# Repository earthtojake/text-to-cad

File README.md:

<div align="center">

Design physical products with AI.

[Website](https://www.texttocad.dev)

</div>

# text-to-cad

## 🚀 Quickstart

macOS and Linux:

```bash
curl -fsSL https://texttocad.dev/install.sh | sh
```

Windows, in PowerShell:

```powershell
irm https://www.texttocad.dev/install.ps1 | iex
```

It installs uv if it is missing, then sets up text-to-cad in every agent app on
your computer with each app's own commands (the plugin, which brings the skills
and CAD's MCP server, or for an agent without a plugin the skills alone; Claude
gets the skills alone and shows models in your browser),
registers the `cad` command, and moves CAD's server to the new release. Run
it again to update everything, or click CAD's update button when it shows one; it
lists the apps to restart.

Then ask your agent for a part or an assembly: it writes the model as a Python
script, runs it to build the model and shows it in the CAD viewer.

Installing by hand, app by app, and updates: [docs/install.md](docs/install.md)

## ✨ Features

The text-to-cad plugin gives your agent local workflows to generate 3D models as STEP, GLB, STL or 3MF files, check them for manufacturing, draw them, and connect to 3D printing, sheet metal and CNC services. It works with any agent that supports plugins or skills.

- [**Parts and assemblies**](skills/cad/SKILL.md): Models written as Python scripts with [build123d](https://github.com/gumyr/build123d) and [OpenCASCADE](https://github.com/Open-Cascade-SAS/OCCT), exported as STEP, STL, 3MF or GLB, and as [DXF profiles and flat patterns](skills/cad/references/2d-profiles-and-dxf.md) for laser and waterjet cutting, with joints and animations for mechanisms, and shown live in the CAD viewer.
- [**Circuit boards**](skills/pcb/SKILL.md): KiCad schematics and boards, placed and routed, checked with ERC and DRC, reviewed before you order, and exported as fabrication files.
- [**Manufacturing checks**](skills/cad/SKILL.md#can-it-be-made): Whether a part can be machined, cut and bent, molded or 3D printed, measured against the process's rules, and what to change where it cannot.
- [**Stress checks**](skills/fea/SKILL.md): Whether a part or an assembly of bonded parts holds under its loads, solved with CalculiX: each part's peak stress, safety factor and how far it moves, drawn on the model.
- [**Engineering drawings**](skills/engineering-drawing/SKILL.md): Dimensioned PDF sheets projected from the part's geometry: views, hidden lines, centre marks, hole callouts and a title block.
- [**Renders**](skills/render/SKILL.md): Photoreal stills, turntables and films of a model with Blender, lit and framed in a Python script and run on the GPU, with a quick draft before each final.
- [**Fabrication services**](skills/sendcutsend/SKILL.md): [Checks DXF and STEP files against SendCutSend's guide](skills/sendcutsend/SKILL.md) before you upload them, and [slices 3D prints](skills/print3d/SKILL.md) with OrcaSlicer and sends them to Bambu Connect or Bambu Studio.
- [**Robotics and simulation**](skills/robot-simulation/SKILL.md): Robot and world descriptions for simulation and motion planning: URDF for ROS, SRDF for MoveIt and MJCF for MuJoCo.

## 🛠️ Contributing

text-to-cad is MIT-licensed and built in the open.

- **Bugs and plugin requests**: [open an issue](https://github.com/earthtojake/text-to-cad/issues/new).
  A bug report with the model script and the output of `cad doctor --check` is the
  fastest to fix, and an agent app without a plugin gets one on request. A
  security problem is reported privately, as [SECURITY.md](SECURITY.md) says.
- **Questions, ideas and what you made**: the [Discord](https://discord.gg/5FGB9DwJYU).
  Say what the skills got wrong, too: that is what improves them.
- **Code, skills and models**: a new skill (a fabrication service, a printer, a
  CAD workflow) goes in `skills/`, an example model in `models/`, and fixes
  anywhere. [CONTRIBUTING.md](CONTRIBUTING.md) has the local setup and how to
  test in the agent apps; an agent working in the repository starts at
  [AGENTS.md](AGENTS.md).

By default, text-to-cad sends usage stats and crash reports, tagged with a random
ID and never including your files, paths or prompts. The
[privacy policy](https://www.texttocad.dev/privacy-policy) says what is sent and
how to turn it off, and the [terms of service](https://www.texttocad.dev/terms-of-service)
govern using text-to-cad.

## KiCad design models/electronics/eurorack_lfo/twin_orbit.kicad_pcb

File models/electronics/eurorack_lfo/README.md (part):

# Twin Orbit: a dual analog LFO for Eurorack, with its panel made from the board

**Build the board first.** Its KiCad files (the board, the three schematic sheets, the footprint library and the
library tables) are generated by `scripts/`, not committed: `cad run build.py`, from this folder, makes them in about
30 s. It needs the `cad` command (KiCad 10.99's kicad-cli and API come with it) and KiCad's stock libraries (macOS's
KiCad.app, or `KICAD10_SYMBOL_DIR` and `KICAD10_FOOTPRINT_DIR`). Opening the board or the schematic in the viewer
or in KiCad, the checks and the panel (`src/`) all read what it writes, so run it before any of them. The project
file, `twin_orbit.kicad_pro`, is kept: it holds the board's rules and netclasses, which no script writes.

Two voltage-controlled low-frequency oscillators in 10HP. Each has a **RATE** knob (exponential, 0.013 Hz to
80 Hz), a **CV** input that sweeps the rate, a **SHAPE** knob that crossfades triangle into square, a red/green
LED that breathes with the triangle, and **TRI**, **SQR** and **MIX** outputs. The board is a 2-layer KiCad
design; the front panel is a build123d model whose every hole is read from the board file, exported as a
laser-cut DXF and checked against SendCutSend's rules for 5052 aluminium.

**Why it is a good demo:** synth people love LFOs, and the story is the panel: *move a jack on the board and the
panel's hole moves with it*, then the panel goes straight to a fabrication service's checks.

## Where it stands

| | |
| --- | --- |
| Schematic | 3 sheets (root, `lfo.kicad_sch` placed twice, `power.kicad_sch`); 76 parts, 45 nets, 227 pins; ERC 0 errors, 0 warnings; KiCad's nets equal the drawn intent pin for pin (`scripts/check_schematic.py`) |
| Board | 48 x 107 mm, 2 layers, 1.6 mm; 76 parts (58 SMD, 62 on the back, panel parts on the front); 235 pads; 495 track segments, 1475 mm of copper track, 85 signal vias + 297 GND vias (290 stitching, 5 in pour islands, 2 on a ground tie); GND poured on both layers |
| DRC | JLCPCB 2-layer standard rules (track 0.25 / space 0.2, rails 0.4, via 0.8/0.4, copper to edge 0.3): **0 errors, 0 unconnected**; 8 warnings, all `lib_footprint_mismatch` on the eight jacks (KiCad's API hands them back with their keepouts' settings changed, which `board_02_keepouts.py` writes back); silkscreen 0 warnings (46 references printed, 30 in the dense expo cluster and under the jacks kept on the Fab layer) |
| Layout checks | `check_twin_orbit.py`: 0 segments off 45 degrees; no two-pad net over 1.6x its straight line; rails 0.4 mm (1.2 A for 10 C rise, 0.1 A needed); board == schematic, 0 differences; decoupling 2.2-5.5 mm from each supply pin except C106/C206, 8.8 mm from the LM13700's V- pin (it sits at pin 10, the buffer input tied to -12 V: a revision would move it) |
| Panel | 10HP x 3U, 2 mm, every hole read from the board; fit: worst overlap 0.000 mm^3 across 50 panel/hardware x board pairs and 435 hardware pairs; bushings clear their holes by 0.15 mm, LEDs by 0.25 mm (`src/check_fit.py`) |
| SendCutSend | the cut DXF in ALU-080 (5052 H32, 0.080"): every cut check passed (2026-11-06: holes, webs, hole to edge, size, units); the engraved legend is a separate file and a separate question |

## The circuit (per LFO; sheet `lfo.kicad_sch`, used twice)

| Block | Parts | What it does |
| --- | --- | --- |
| Exponential current source | Q101/Q102 BC857B pair, U101 section 1 (TL074) servo, R105 5.6 M, C101 100 p, D101 clamp | Iabc = 2.1 uA x exp(V(QB)/26 mV); RATE (B100k across the rails, 33k) and CV (33k) sum at the base node over 220 ohm |
| OTA integrator | U102 LM13700 (one OTA used, the other terminated), C102 100 nF C0G | the square (divided to +-260 mV by R111/R113) saturates the OTA, which charges C102 with +-Iabc: a linear triangle |
| Buffer and Schmitt | U101 sections 4 (follower) and 2 (Schmitt), R106 47k / R107 56k, R110 1k, D102 AZ23C5V1 | square clamped to +-5.8 V; triangle +-4.87 V; f = Iabc / (4 C2 Vp) = 1.0 Hz at 2 uA |
| Outputs | U101 section 3 (MIX follower), RV102 SHAPE B100k, R108/R112/R114 1k, Thonkiconn PJ398SM x 4, R109 2.2k + bicolour LED | TRI, SQR and the SHAPE crossfade, each through 1 k |

Power (`power.kicad_sch`): shrouded 2x5 Eurorack header (pin 1 = -12 V, red stripe), SS14 Schottky in each rail
(reverse ribbon blocks; 0.35 V drop at the ~25 mA the module draws), BLM21 220 ohm ferrite and 10 uF 25 V X7R bulk
per rail, 100 nF at every supply pin, test points for +12 V, -12 V and GND.

## Key parts

| Ref | Part | MPN |
| --- | --- | --- |
| U101, U201 | quad JFET op-amp | TI TL074CDR (SOIC-14) |
| U102, U202 | dual OTA | TI LM13700MX/NOPB (SOIC-16) |
| Q101-Q202 | PNP | Nexperia BC857B (SOT-23) |
| J101-J204 | 3.5 mm jack | Thonkiconn PJ398SM |
| RV101-RV202 | 9 mm vertical pot B100k | Alpha RD901F-40-15R1 |
| D103, D203 | 3 mm bicolour LED | Kingbright WP3VEGW, on a 3.5 mm spacer |
| J1 | 2x5 shrouded header | Sullins SBH11-PBPC-D05-ST-BK |

KiCad's library names a 3D model for the PJ398SM jack and the 9 mm pots but ships none, so
`src/footprint_models.py` draws both (from Thonk's and Alpha's drawings) and the project's copies of their
footprints (`twin_orbit.pretty`) name them under `${KIPRJMOD}/3dmodels`. The LED's footprint is KiCad's with its
model raised 3.6 mm, the spacer that brings the dome to the panel: KiCad's `LED_D3.0mm` model is 9.9 mm tall,
taller than a datasheet LED's body.

## Mechanics

10HP x 3U panel (50.5 x 128.5 mm, Doepfer A-100), 2 mm 5052 H32 (SendCutSend ALU-080, 0.080"), black anodised,
white legend. The board (48 x 107 mm) sits 10.0 mm behind the panel's back face: the pots' mounting face. The
jacks are 9.0 mm bodies with a 0.5 mm collar, so each gets a 0.5 mm spacer washer. Rail slots 3.2 x 5.2 mm at
x = 7.5 and 43.06 mm, 3.0 mm from the top and bottom edges. Holes: jacks 6.3, pots 7.3, LEDs 3.5 mm.
Hardware modelled: Davies 1900H-style knobs, M6 hex nuts (jacks), M7 hex nuts (pots), spacers.

## How the board was routed

`scripts/board_03_route.py` routes it with `cad.kicad.route`, the library's router the pcb skill directs, as its plan directs: the
order of the nets (each LFO's integrator node and rate wiper and the -12 V rail first, because they walled other
connections in when they came later; then every other net, the shortest first; last the ground ties), the layer
each keeps to (the back, a millimetre on the front costing 2.5, but +12V on the front) and what a via costs (2.5 mm
of track). The router routes only what the plan names, round everything on the board, by the board's own rules
(the netclasses' widths and clearances, the edge, the jacks' keepouts), and checks every segment and via exactly
before it writes them through the edit. A connection it cannot route is said with what walls it in, and that is
how the plan's first five nets were chosen; its last tie, LFO A's TL074 pin 3 to pin 6, is there because DRC
found that pin's patch of pour joined to nothing else.

The plan's 115 connections route in about 2 s (the step, with KiCad's start and save, in about 5 s): 495 segments,
1475 mm of track and 87 vias. Before the tool, this project routed the board with a search of its own
(`assist_route.py`, since deleted with its `routelib.py`, `route_plan.json`, `routes.json` and
`board_03_sync.py`): about three minutes for 538 segments, 1354 mm of track and 115 vias.

Moving a footprint over KiCad's API leaves its own keepout zones behind (KiPy moves a footprint zone's outline
by the move in the footprint's frame), so `scripts/board_02_keepouts.py` writes each jack's keepout back as the
library footprint has it, in the footprint's own frame, after every placement: KiCad 11 holds a footprint's zones
there and places them with it, so the router, the stitching and the front pour keep out of each jack's circle.

## Files

| Path | What |
| --- | --- |
| `build.py` | the one command that makes the KiCad project: every step of `scripts/` in order |
| `scripts/` | the source of the board: libraries, schematic (and its intent, `schematic_intent.json`), netlist import, placement (`place_table.py`), routing (`board_03_route.py`, the plan), pours, silkscreen |
| `twin_orbit.kicad_pro` | the project file (KiCad 10.99 format): the board's rules and netclasses, set by hand, the only KiCad file kept |
| `check_twin_orbit.py` | the board's own checks |
| `src/` | the panel and its hardware: `footprint_models.py` (the jack and the pot), `hardware.py`, `panel.py`, `assembly.py`, `check_fit.py`, `check_dxf.py`, `exports.py`, `lib/twin_orbit.py` (what they read from the board) |

Nothing generated is committed: the KiCad files `build.py` writes (`twin_orbit.kicad_pcb`, `twin_orbit.kicad_sch`
and its `lfo` and `power` sheets, `twin_orbit.pretty/`, `fp-lib-table` and `sym-lib-table`, which name KiCad's stock
libraries through `${KICAD10_FOOTPRINT_DIR}` and `${KICAD10_SYMBOL_DIR}`), the footprints' 3D models (`3dmodels/`),
the fabrication files (`fab/`), the board's STEP and the panel's and assembly's files (`STEP/`, `GLB/`, `DXF/`) are
written by the commands below, and `.gitignore` keeps them out of Git.

## Rebuild

From this folder, with the `cad` command. KiCad's stock libraries are named through `${KICAD10_SYMBOL_DIR}` and
`${KICAD10_FOOTPRINT_DIR}`, which ERC and DRC read in the KiCad you installed: nothing to set. The generators
(`make_libs.py`, `gen_schematic.py`) read the same libraries in macOS's KiCad.app; elsewhere, give them KiCad's
folders in those two variables.

```bash
# the board and its schematic, from scripts/ (each step states the board it wants; rerunning is harmless)
cad run build.py                                # about 30 s: the steps below, in order
#   scripts/make_libs.py                        twin_orbit.pretty and the library tables
#   scripts/gen_schematic.py                    root, LFO (x2) and power sheets
#   scripts/board_01_import.py                  netlist -> board (KiCad makes it beside twin_orbit.kicad_pro)
#   scripts/board_02_place.py                   outline + placement (scripts/place_table.py)
#   scripts/board_02_keepouts.py                the jacks' own keepouts back over the jacks
#   scripts/board_03_route.py                   tracks + vias: the plan, routed by cad.kicad.route (about 5 s)
#   scripts/board_04_pour.py                    GND pours both layers + stitching
#   scripts/board_05_islands.py                 a via in any pour piece left without one
#   cad kicad_pcb drc ... --json                tmp/drc_before_cleanup.json, what the cleanup reads
#   scripts/board_06_cleanup.py                 vias DRC calls dangling, same-net vias too close
#   scripts/board_07_silk.py                    every reference to a free spot, or onto the Fab layer

# the 3D models KiCad's library lacks: run this before opening the board in 3D or exporting its STEP or GLB
cad run src/footprint_models.py                 # 3dmodels/: the PJ398SM jack and the RD901F pot

# check the board
cad kicad_sch erc twin_orbit.kicad_sch
cad run scripts/check_schematic.py              # KiCad's nets == the drawn intent, both instances
cad kicad_pcb drc twin_orbit.kicad_pcb
cad run check_twin_orbit.py                     # prints nothing when the board is clean

# fabrication (JLCPCB 2-layer)
for k in gerbers drill pos bom pdf; do cad kicad_pcb export twin_orbit.kicad_pcb --to $k -o fab/$k; done
(cd fab && zip -qr gerbers_jlcpcb.zip gerbers drill)
cad kicad_sch export twin_orbit.kicad_sch --to pdf -o fab/schematic
cad kicad_pcb export twin_orbit.kicad_pcb --to glb -o GLB      # the board with its parts, to look at

# the panel, read from the board: the board's STEP with its origin at the board's top-left corner
cad run kicad-cli pcb export step --force --subst-models --user-origin 100x50mm -o STEP/twin_orbit.step twin_orbit.kicad_pcb
cad run src/hardware.py && cad run src/panel.py && cad run src/assembly.py
cad run src/check_fit.py                        # zero overlap, the intended clearances
cad run src/exports.py                          # DXF/ panel cut and art, STEP/ panel, assembly and hardware, GLB/ assembly
cad run src/check_dxf.py                        # the cut DXF's facts, for a SendCutSend preflight
```

`make_libs.py` and `gen_schematic.py` write the same files on every run. The layout steps
make the same placement and the same copper again (the router gives the same tracks and vias for the same board
and plan, and the stitching follows them); DRC and the check stay clean.

## Demo video script (about 3 minutes)

The thread to keep: **the panel is made from the board.** Every shot builds toward shot 6, where a jack moves on
the board and the panel's hole follows, and shot 7, where the panel goes to a fabrication service's checks.
Record in an agent app with text-to-cad installed and this folder open; the viewer pages are `cad viewer` pages.

| # | Prompt the person types | What the viewer shows | Length | The one impressive thing |
| --- | --- | --- | --- | --- |
| 1 | "Design a Eurorack dual LFO: rate and shape knobs, CV in, triangle, square and mix outs, a bicolour LED, 10HP." | The schematic opening on its root sheet, then the Hierarchy: LFO A, LFO B, Power | 20 s | One LFO sheet placed twice: LFO B is the same circuit with 2xx references |
| 2 | "Walk me through how the rate works." | LFO A's sheet; the Nets tab picks net `/LFO A/QB`, the expo pair lights | 25 s | A real exponential converter servoed by an op-amp feeding an LM13700, with the maths on the sheet (0.013-80 Hz) |
| 3 | "Run ERC and check every pin landed on the right net." | Terminal: ERC clean (0 warnings); the pin-by-pin check: 0 mismatches | 10 s | The agent proves the schematic before touching copper |
| 4 | "Show me the board." | Board in 2D: copper front, then Flip for the bottom, the side with the ICs; Display > copper | 25 s | 2-layer, both GND pours stitched, DRC clean against JLCPCB's standard rules |
| 5 | "Now in 3D." | The corner's 2D/3D button: jacks, Alpha pots, LEDs and the shrouded header in place, every part on its model | 15 s | Every part has a 3D model; the jack and pot models the KiCad library lacks were drawn by the agent with the cad skill |
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
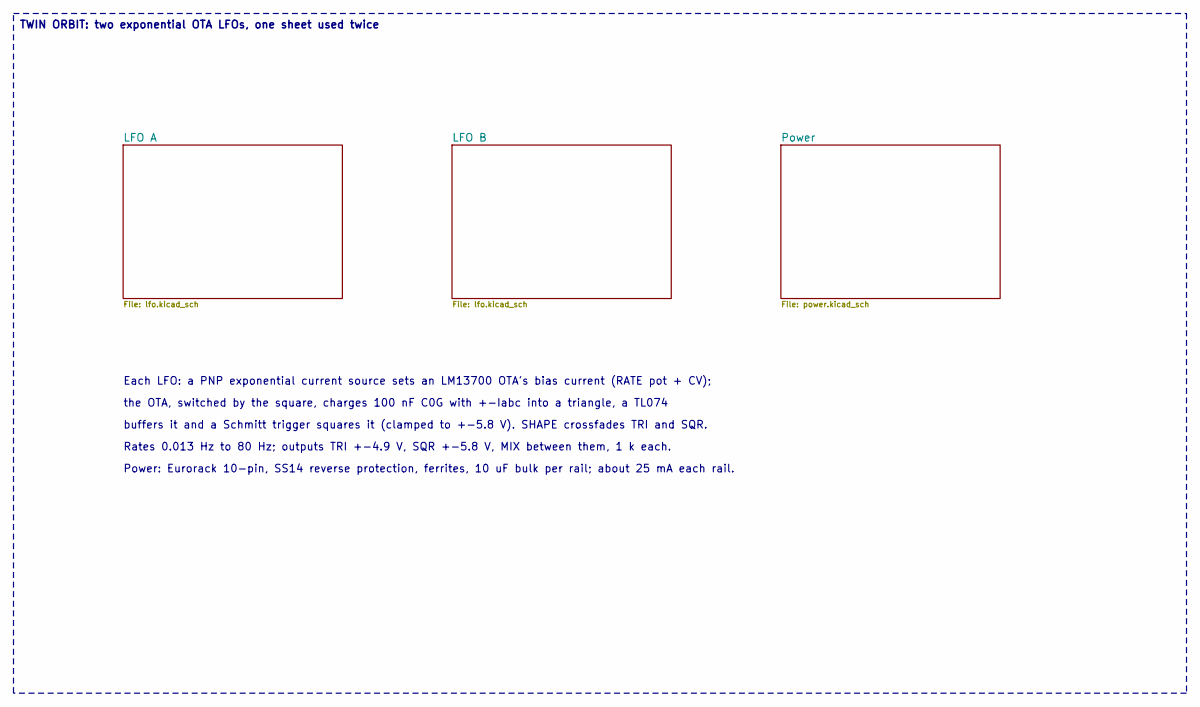
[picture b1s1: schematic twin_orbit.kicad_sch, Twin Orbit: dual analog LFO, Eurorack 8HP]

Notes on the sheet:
TWIN ORBIT: two exponential OTA LFOs, one sheet used twice
Each LFO: a PNP exponential current source sets an LM13700 OTA's bias current (RATE pot + CV);
the OTA, switched by the square, charges 100 nF C0G with +-Iabc into a triangle, a TL074
buffers it and a Schmitt trigger squares it (clamped to +-5.8 V). SHAPE crossfades TRI and SQR.
Rates 0.013 Hz to 80 Hz; outputs TRI +-4.9 V, SQR +-5.8 V, MIX between them, 1 k each.
Power: Eurorack 10-pin, SS14 reverse protection, ferrites, 10 uF bulk per rail; about 25 mA each rail.

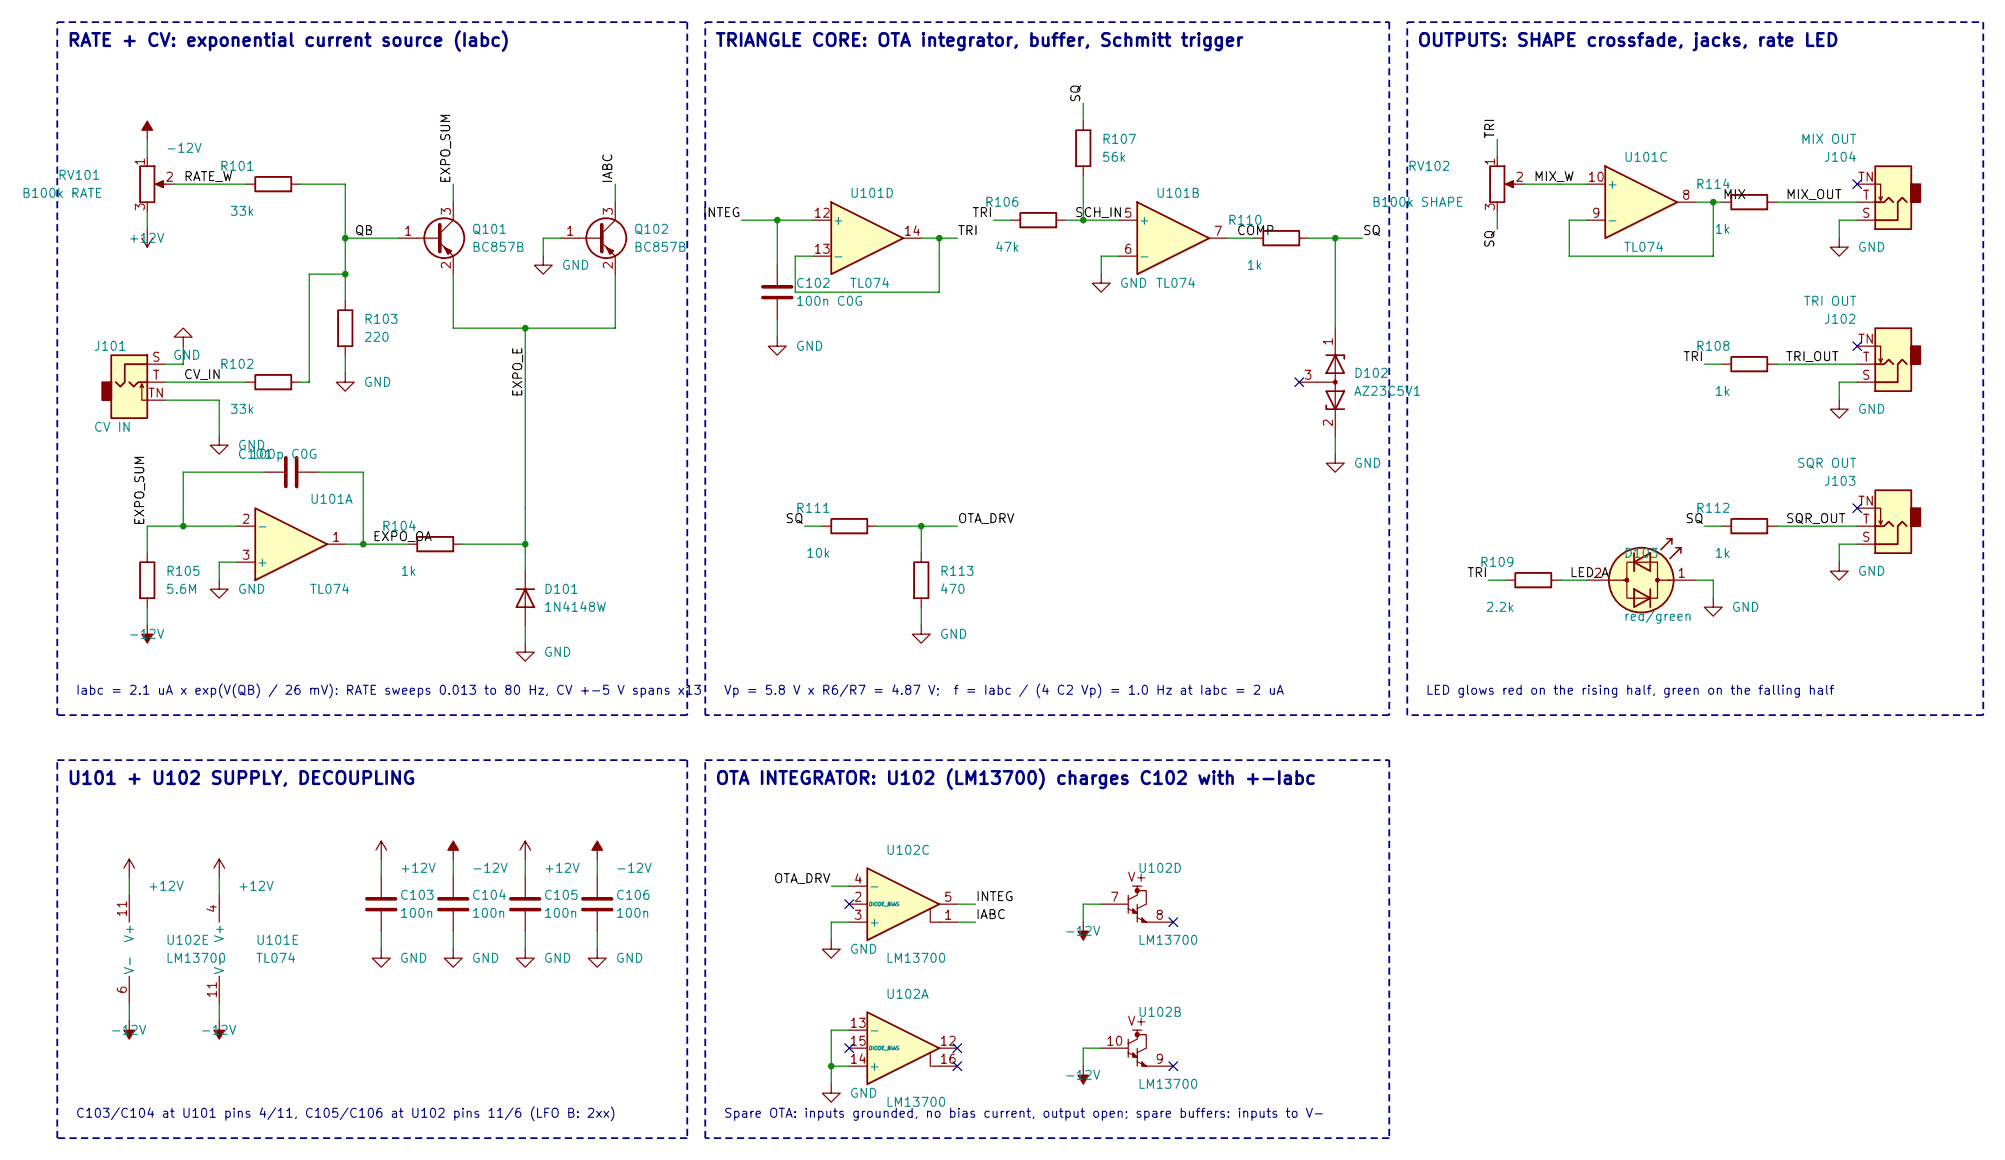
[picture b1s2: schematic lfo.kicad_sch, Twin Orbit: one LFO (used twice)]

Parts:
C101: 100p C0G; C_0603_1608Metric; MPN GRM1885C1H101JA01D
C102: 100n C0G; C_1206_3216Metric; MPN GRM31C5C1H104JA01L
C103, C104, C105, C106: 100n; C_0603_1608Metric; MPN CL10B104KB8NNNC
D101: 1N4148W; D_SOD-123; MPN 1N4148W-7-F
D102: AZ23C5V1; SOT-23; MPN AZ23C5V1-7-F
D103: red/green; LED_D3.0mm_Spacer3.5mm; MPN WP3VEGW
J101: CV IN; Jack_3.5mm_QingPu_WQP-PJ398SM_Vertical_CircularHoles; MPN PJ398SM
J102: TRI OUT; Jack_3.5mm_QingPu_WQP-PJ398SM_Vertical_CircularHoles; MPN PJ398SM
J103: SQR OUT; Jack_3.5mm_QingPu_WQP-PJ398SM_Vertical_CircularHoles; MPN PJ398SM
J104: MIX OUT; Jack_3.5mm_QingPu_WQP-PJ398SM_Vertical_CircularHoles; MPN PJ398SM
Q101, Q102: BC857B; SOT-23; MPN BC857B,215
R101, R102: 33k; R_0603_1608Metric; MPN RC0603FR-0733KL
R103: 220; R_0603_1608Metric; MPN RC0603FR-07220RL
R104, R108, R110, R112, R114: 1k; R_0603_1608Metric; MPN RC0603FR-071KL
R105: 5.6M; R_0603_1608Metric; MPN RC0603FR-075M6L
R106: 47k; R_0603_1608Metric; MPN RC0603FR-0747KL
R107: 56k; R_0603_1608Metric; MPN RC0603FR-0756KL
R109: 2.2k; R_0603_1608Metric; MPN RC0603FR-072K2L
R111: 10k; R_0603_1608Metric; MPN RC0603FR-0710KL
R113: 470; R_0603_1608Metric; MPN RC0603FR-07470RL
RV101: B100k RATE; Potentiometer_Alpha_RD901F-40-00D_Single_Vertical; MPN RD901F-40-15R1-B100K
RV102: B100k SHAPE; Potentiometer_Alpha_RD901F-40-00D_Single_Vertical; MPN RD901F-40-15R1-B100K
U101: TL074; SOIC-14_3.9x8.7mm_P1.27mm; MPN TL074CDR
U102: LM13700; SOIC-16_3.9x9.9mm_P1.27mm; MPN LM13700MX/NOPB

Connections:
+12V: C103.1, C105.1, RV101.3, U101.4 (V+), U102.11 (V+); also elsewhere on the board
-12V: C104.1, C106.1, R105.2, RV101.1, U101.11 (V-), U102.6 (V-), U102.7, U102.10; also elsewhere on the board
/LFO A/COMP: R110.1, U101.7
/LFO A/CV_IN: J101.T, R102.1
/LFO A/EXPO_E: D101.1 (K), Q101.2 (E), Q102.2 (E), R104.2
/LFO A/EXPO_OA: C101.2, R104.1, U101.1
/LFO A/EXPO_SUM: C101.1, Q101.3 (C), R105.1, U101.2 (-)
/LFO A/IABC: Q102.3 (C), U102.1
/LFO A/INTEG: C102.1, U101.12 (+), U102.5
/LFO A/LED_A: D103.2 (AK), R109.2
/LFO A/MIX: R114.1, U101.8, U101.9 (-)
/LFO A/MIX_OUT: J104.T, R114.2
/LFO A/MIX_W: RV102.2, U101.10 (+)
/LFO A/OTA_DRV: R111.2, R113.1, U102.4 (-)
/LFO A/QB: Q101.1 (B), R101.2, R102.2, R103.1
/LFO A/RATE_W: R101.1, RV101.2
/LFO A/SCH_IN: R106.2, R107.2, U101.5 (+)
/LFO A/SQ: D102.1 (K), R107.1, R110.2, R111.1, R112.1, RV102.3
/LFO A/SQR_OUT: J103.T, R112.2
/LFO A/TRI: R106.1, R108.1, R109.1, RV102.1, U101.13 (-), U101.14
/LFO A/TRI_OUT: J102.T, R108.2
GND: C102.2, C103.2, C104.2, C105.2, C106.2, D101.2 (A), D102.2 (K), D103.1 (KA), J101.S, J101.TN, J102.S, J103.S, J104.S, Q102.1 (B), R103.2, R113.2, U101.3 (+), U101.6 (-), U102.3 (+), U102.13 (-), U102.14 (+); also elsewhere on the board

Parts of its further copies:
C201: 100p C0G; C_0603_1608Metric; MPN GRM1885C1H101JA01D
C202: 100n C0G; C_1206_3216Metric; MPN GRM31C5C1H104JA01L
C203, C204, C205, C206: 100n; C_0603_1608Metric; MPN CL10B104KB8NNNC
D201: 1N4148W; D_SOD-123; MPN 1N4148W-7-F
D202: AZ23C5V1; SOT-23; MPN AZ23C5V1-7-F
D203: red/green; LED_D3.0mm_Spacer3.5mm; MPN WP3VEGW
J201: CV IN; Jack_3.5mm_QingPu_WQP-PJ398SM_Vertical_CircularHoles; MPN PJ398SM
J202: TRI OUT; Jack_3.5mm_QingPu_WQP-PJ398SM_Vertical_CircularHoles; MPN PJ398SM
J203: SQR OUT; Jack_3.5mm_QingPu_WQP-PJ398SM_Vertical_CircularHoles; MPN PJ398SM
J204: MIX OUT; Jack_3.5mm_QingPu_WQP-PJ398SM_Vertical_CircularHoles; MPN PJ398SM
Q201, Q202: BC857B; SOT-23; MPN BC857B,215
R201, R202: 33k; R_0603_1608Metric; MPN RC0603FR-0733KL
R203: 220; R_0603_1608Metric; MPN RC0603FR-07220RL
R204, R208, R210, R212, R214: 1k; R_0603_1608Metric; MPN RC0603FR-071KL
R205: 5.6M; R_0603_1608Metric; MPN RC0603FR-075M6L
R206: 47k; R_0603_1608Metric; MPN RC0603FR-0747KL
R207: 56k; R_0603_1608Metric; MPN RC0603FR-0756KL
R209: 2.2k; R_0603_1608Metric; MPN RC0603FR-072K2L
R211: 10k; R_0603_1608Metric; MPN RC0603FR-0710KL
R213: 470; R_0603_1608Metric; MPN RC0603FR-07470RL
RV201: B100k RATE; Potentiometer_Alpha_RD901F-40-00D_Single_Vertical; MPN RD901F-40-15R1-B100K
RV202: B100k SHAPE; Potentiometer_Alpha_RD901F-40-00D_Single_Vertical; MPN RD901F-40-15R1-B100K
U201: TL074; SOIC-14_3.9x8.7mm_P1.27mm; MPN TL074CDR
U202: LM13700; SOIC-16_3.9x9.9mm_P1.27mm; MPN LM13700MX/NOPB

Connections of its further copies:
+12V: C203.1, C205.1, RV201.3, U201.4 (V+), U202.11 (V+); also elsewhere on the board
-12V: C204.1, C206.1, R205.2, RV201.1, U201.11 (V-), U202.6 (V-), U202.7, U202.10; also elsewhere on the board
/LFO B/COMP: R210.1, U201.7
/LFO B/CV_IN: J201.T, R202.1
/LFO B/EXPO_E: D201.1 (K), Q201.2 (E), Q202.2 (E), R204.2
/LFO B/EXPO_OA: C201.2, R204.1, U201.1
/LFO B/EXPO_SUM: C201.1, Q201.3 (C), R205.1, U201.2 (-)
/LFO B/IABC: Q202.3 (C), U202.1
/LFO B/INTEG: C202.1, U201.12 (+), U202.5
/LFO B/LED_A: D203.2 (AK), R209.2
/LFO B/MIX: R214.1, U201.8, U201.9 (-)
/LFO B/MIX_OUT: J204.T, R214.2
/LFO B/MIX_W: RV202.2, U201.10 (+)
/LFO B/OTA_DRV: R211.2, R213.1, U202.4 (-)
/LFO B/QB: Q201.1 (B), R201.2, R202.2, R203.1
/LFO B/RATE_W: R201.1, RV201.2
/LFO B/SCH_IN: R206.2, R207.2, U201.5 (+)
/LFO B/SQ: D202.1 (K), R207.1, R210.2, R211.1, R212.1, RV202.3
/LFO B/SQR_OUT: J203.T, R212.2
/LFO B/TRI: R206.1, R208.1, R209.1, RV202.1, U201.13 (-), U201.14
/LFO B/TRI_OUT: J202.T, R208.2
GND: C202.2, C203.2, C204.2, C205.2, C206.2, D201.2 (A), D202.2 (K), D203.1 (KA), J201.S, J201.TN, J202.S, J203.S, J204.S, Q202.1 (B), R203.2, R213.2, U201.3 (+), U201.6 (-), U202.3 (+), U202.13 (-), U202.14 (+); also elsewhere on the board

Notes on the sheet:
RATE + CV: exponential current source (Iabc)
Iabc = 2.1 uA x exp(V(QB) / 26 mV): RATE sweeps 0.013 to 80 Hz, CV +-5 V spans x13
TRIANGLE CORE: OTA integrator, buffer, Schmitt trigger
Vp = 5.8 V x R6/R7 = 4.87 V; f = Iabc / (4 C2 Vp) = 1.0 Hz at Iabc = 2 uA
OUTPUTS: SHAPE crossfade, jacks, rate LED
LED glows red on the rising half, green on the falling half
OTA INTEGRATOR: U102 (LM13700) charges C102 with +-Iabc
Spare OTA: inputs grounded, no bias current, output open; spare buffers: inputs to V-
U101 + U102 SUPPLY, DECOUPLING
C103/C104 at U101 pins 4/11, C105/C106 at U102 pins 11/6 (LFO B: 2xx)

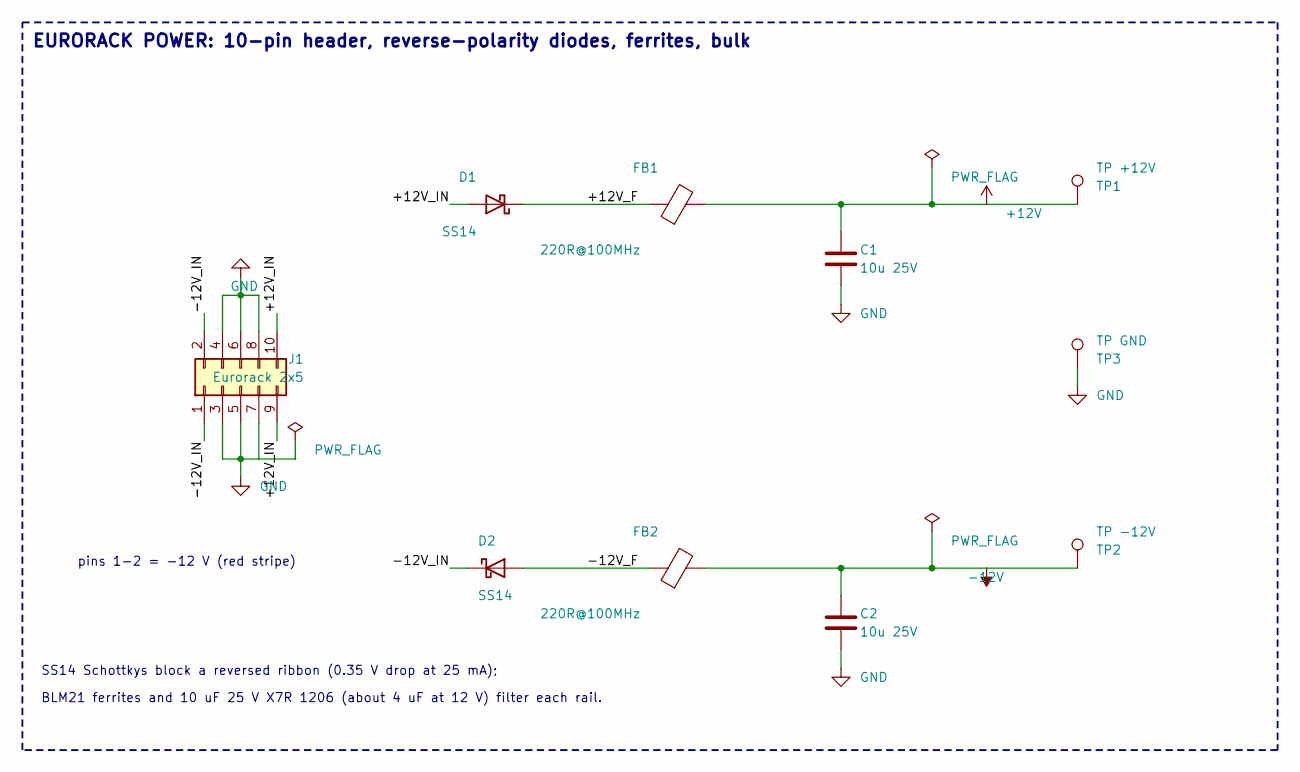
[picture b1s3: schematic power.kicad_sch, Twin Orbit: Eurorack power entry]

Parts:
C1, C2: 10u 25V; C_1206_3216Metric; MPN CL31B106KAHNNNE
D1, D2: SS14; D_SMA; MPN SS14
FB1, FB2: 220R@100MHz; L_0805_2012Metric; MPN BLM21PG221SN1D
J1: Eurorack 2x5; IDC-Header_2x05_P2.54mm_Vertical; MPN SBH11-PBPC-D05-ST-BK
TP1: TP +12V; TestPoint_Keystone_5005-5009_Compact; MPN 5005
TP2: TP -12V; TestPoint_Keystone_5005-5009_Compact; MPN 5007
TP3: TP GND; TestPoint_Keystone_5005-5009_Compact; MPN 5006

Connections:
+12V: C1.1, FB1.2, TP1.1 (1_1); also elsewhere on the board
-12V: C2.1, FB2.2, TP2.1 (1_1); also elsewhere on the board
/Power/+12V_F: D1.1 (K), FB1.1
/Power/+12V_IN: D1.2 (A), J1.9, J1.10
/Power/-12V_F: D2.2 (A), FB2.1
/Power/-12V_IN: D2.1 (K), J1.1, J1.2
GND: C1.2, C2.2, J1.3, J1.4, J1.5, J1.6, J1.7, J1.8, TP3.1 (1_1); also elsewhere on the board

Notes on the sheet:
EURORACK POWER: 10-pin header, reverse-polarity diodes, ferrites, bulk
pins 1-2 = -12 V (red stripe)
SS14 Schottkys block a reversed ribbon (0.35 V drop at 25 mA);
BLM21 ferrites and 10 uF 25 V X7R 1206 (about 4 uF at 12 V) filter each rail.

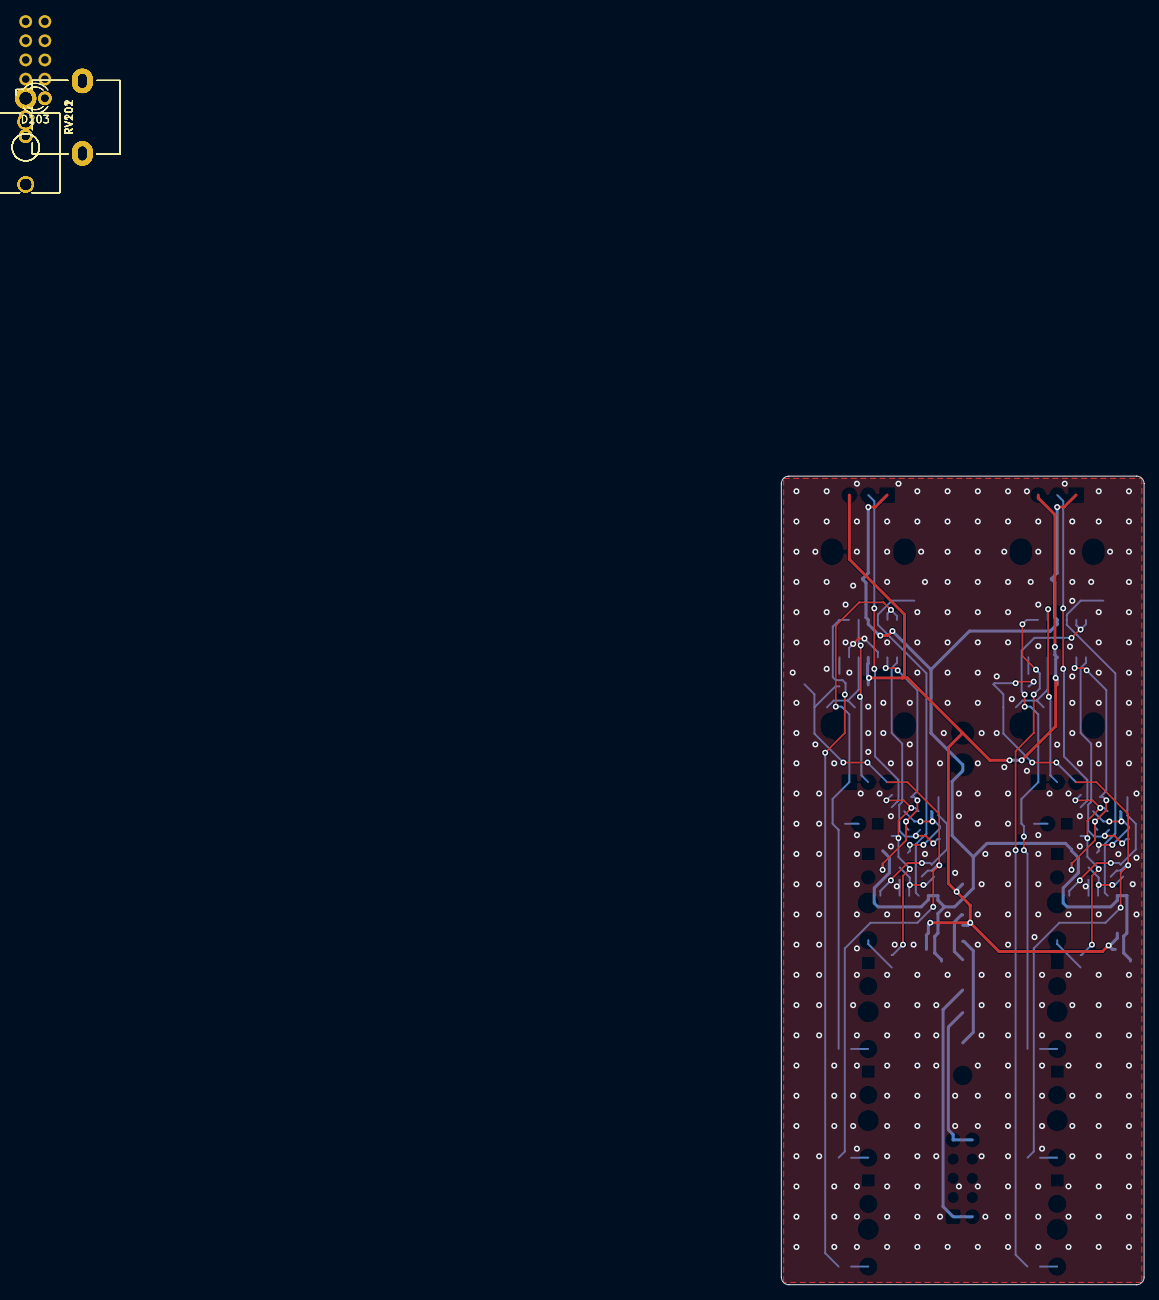
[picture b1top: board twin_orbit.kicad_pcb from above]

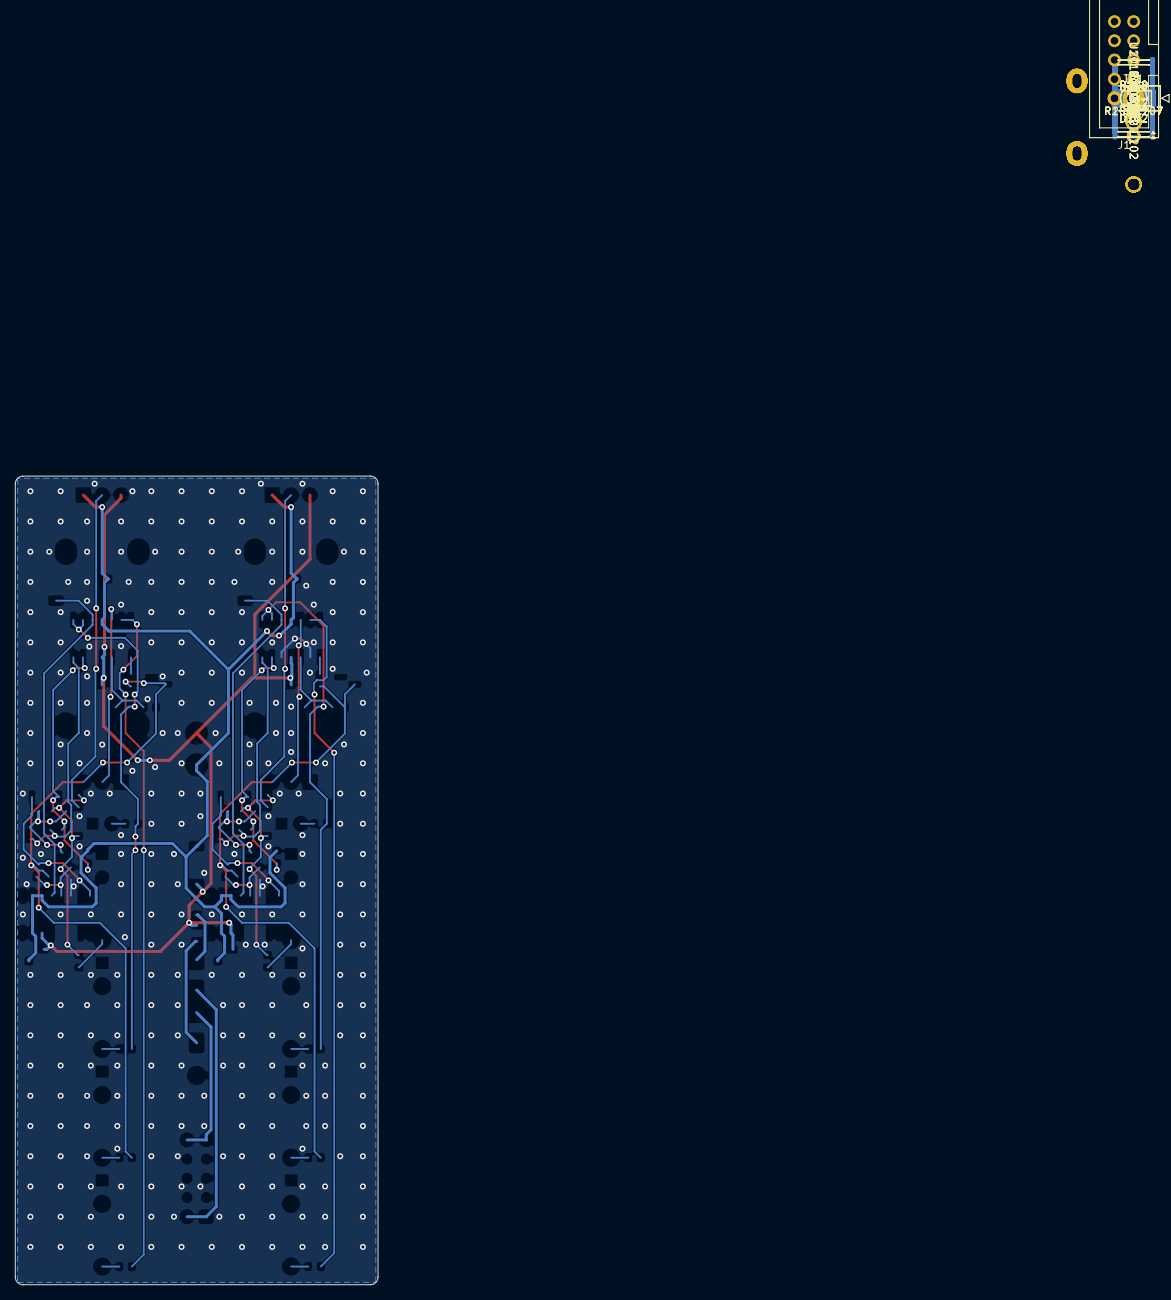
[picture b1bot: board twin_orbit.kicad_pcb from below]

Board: 2 copper layers, 48.0 x 107.0 mm, 76 parts (62 on the bottom side), 45 nets.

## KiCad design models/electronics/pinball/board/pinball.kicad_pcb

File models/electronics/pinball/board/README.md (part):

# SHORT CIRCUIT: the playfield board

**Build the board first.** Its KiCad files (the board, the seven schematic sheets, the project file and its custom
rules, the project libraries and their tables) are generated from the design model by `scripts/`, not committed:
`cad run build.py`, from this folder, makes them in about eight minutes, most of it the routes' plan. It needs the
`cad` command (KiCad 10.99's kicad-cli and API come with it) and KiCad's stock libraries (macOS's KiCad.app, or
`KICAD_STOCK`). Opening the board or the schematic in the viewer or in KiCad, `check_board.py` and
`check_fit.py` all read what it writes, so run it before any of them.

The playfield of the SHORT CIRCUIT pinball machine is this circuit board: its gold art is the machine's switches (the
steel ball shorts a comb of two nets), its parts live on the underside, and its outline, holes and art come from the
design model's numbers (`../src/layout.py`, `../src/playfield.py`) through `scripts/geometry.py`.

| | |
| --- | --- |
| Board | 112 x 236 x 1.6 mm, corners r 4, 4 layers (F.Cu art, In1 ground, In2 and B.Cu wiring), ENIG, black mask, the CAD model's outline |
| Parts | 250 footprints: 189 to assemble (38 LEDs, RP2040, flash, CH224K, TPS563201, AP2112K, 74AHCT1G125, MAX98357A, LIS3DH, USBLC6-2SC6, AO3400A x 2, SS34 x 2, 18 TVS, the connectors and passives), 18 ball switches, 33 holes, 6 fiducials, 4 SWD test pads |
| Nets | 125 |
| Routing | every net: 2055 track segments, 6.80 m of copper, 514 vias (369 the wiring's, 145 the art's stitching) |
| ERC | clean: 0 errors, 0 warnings (`cad kicad_sch erc`) |
| DRC | clean: 0 errors, 14 warnings (`cad kicad_pcb drc` on the built board, the project's rules; the warnings are listed below) |
| Fit | `check_fit.py` passes, 0 failures: outline, flipper bores, every fixing hole under its part, every insert's LED under its window, the combs against `playfield.py`, every top part hidden under furniture, the underside clear of the flipper mechanisms |
| Own checks | `check_board.py` clean: 630 pins, 0 differ from the schematic; 0 segments off 45 degrees; each rail's width for its peak current (IPC-2221, 10 C rise); each supply pin's capacitor distance; In1 under the whole USB pair (D+ 42.7 mm, D- 44.8 mm) |
| Rules | JLCPCB standard 4-layer from the pcb skill's table (read 2026-11-04): 0.15 mm clearance (fab 0.09), 0.2 mm signal, 0.3/0.6 mm vias, 0.3 mm copper to edge, 0.25 mm hole clearance; a custom rule each for the combs' chevrons (0.1 mm, `pinball.kicad_dru`), the stock SK6812MINI-E's own cut-out (0.2 mm to its edge) and the RP2040's fan-out (0.15 mm tracks under the package) |

## The design, sheet by sheet

**Power** (`power.kicad_sch`). USB-C (HRO TYPE-C-31-M-12, J1) -> 2 A polyfuse (F1) -> CH224K (U3) asks the charger for
9 V (6.8k on CFG1, R3) -> TPS563201 buck (U5) to 5 V (56k/10k: 0.768 V x 6.6 = 5.07 V) -> AP2112K-3.3 (U6). The USB pair
runs through a USBLC6-2SC6 (U4), the ESD clamp at the connector. A 100k/22k divider (R7/R8) lets the firmware read the
9 V rail on GPIO29 (ADC3).

**MCU** (`mcu.kicad_sch`). RP2040 (U1), W25Q128JVS flash (U2), 12 MHz crystal (Y1, 15 pF loads, 1k on XOUT), 27 ohm
series resistors on D+ and D- (R10/R11), BOOTSEL (SW1, through 1k on QSPI_SS) and RESET (SW2), SWD on test pads
(TP1..TP4), I2C pull-ups (R14/R15). Every GPIO has a job; the map (`geometry.gpio_map`) gives each signal the pin that
travels least to where it goes, after the silicon's own constraints (I2C1 on GP18/19, the PIO I2S pair on GP20/21, ADC on
GP29).

**Inputs** (`inputs.kicad_sch`). The 18 ball switches (S1..S18): each comb is two nets, `SENSE_*` and GND, 0.4 mm
fingers on a 0.8 mm pitch; the 8 mm steel ball bridges them. The combs are exposed metal, so each has a TVS
(PESD5V0S1BA, D3..D20) at its land and a 1k (R50..R67) beside it; the line on to the RP2040 (`IN_*`) is pulled up inside
the chip. The flipper buttons (SW3/SW4, in the rails) and START (SW5, in the lockdown bar) go straight to GPIO; the
tilt is an LIS3DH (U9) on I2C.

**Lighting** (`lighting.kicad_sch`). 38 addressable LEDs in one chain: reverse-mount SK6812MINI-E under the inserts
(each in a cut-out, shining up through the board), WS2812B-2020 under the bumpers, slings and targets and as underglow.
The RP2040's 3.3 V data goes through a 74AHCT1G125 (U7: VIH 2 V, so 3.3 V is a clean high; it drives a full 5 V edge,
which the chain needs: its VIH is 0.7 VDD = 3.5 V) with a 33 ohm series resistor (R20) at its output; C50 decouples it,
C51 (220 uF) holds the LED rail, and every LED has its own 100 nF (C101..C138).

**Flippers** (`flippers.kicad_sch`). Each coil (Takaha CA07300160, 16 ohm, 0.56 A at 9 V) is switched low-side by an
AO3400A (Q1/Q2) with a 100 ohm gate resistor (R30/R32) and a 10k pull-down (R31/R33) that holds it off while the RP2040
boots; an SS34 (D1/D2) across each coil catches the flyback. C60 (220 uF) and C61/C62 (10 uF) at the drivers carry the
pulse.

**Audio and backbox** (`audio.kicad_sch`). MAX98357A (U8, I2S, mono (L+R)/2 by its SD_MODE resistor R40) to speaker
pads (J5) and to the backbox link (J4, JST SH: +5V, I2C, speaker, GND).

## The layout

- **F.Cu is the art**: the gold combs on their nets, the pinstripes, the radiance and the letters, copper with the mask
  opened over it so the ball rolls over gold on black. The stitching vias the art draws are real: GND vias through to
  In1. In1 is a whole ground plane; In2 and B.Cu carry the wiring, each poured with ground round it.
- **The RP2040's supply pins** (U1) each run inward under the package to a via in the ring between the pads and the
  exposed pad; each pin's capacitor stands on the top copper over its via, its supply pad 0.4 to 0.9 mm from the pin
  (C20..C31: the loop is the board's thickness), under the backbox where there is no art, its ground in a patch of
  top-copper ground. C26 and C28 (a second 100 nF and VREG_VIN's 1 uF) stand at the package's corners, 9 to 11 mm out. Under U1 on
  In2 an island of 3V3 joins the supply vias; the 1V1 vias (VREG_VOUT to the two DVDD pins) are joined by hand on In2.
  The signal pins fan out to a 0.8 mm pitch on B.Cu; on the side facing the field each long line may drop to In2 at the
  end of its lane.
- **The USB pair** is routed by hand (`routes.usb_pair`): the connector's two rows joined (D- over the top of the pad row,
  D+ under it), straight through U4's flow-through pins, then side by side (0.2 mm tracks, 0.2 mm apart, over the In1
  plane) to R10/R11 and U1.
- **Currents.** VBUS and +9V run on 1.0 mm tracks (2.39 A at a 10 C rise by IPC-2221, against a 2.02 A peak), the coils'
  drains and the buck's switch node on 0.8 mm, the 5 V rail on 0.6 mm (1.65 A against 1.45 A); each necks to 0.3 mm only
  within 1.6 mm of a pad, and the LED branches run at 0.3 mm.
- **Ground**: every ground pad on the underside has its own via to In1 beside it, never in the pad (the exposed pads'
  thermal vias excepted; the MAX98357A's ground pins join its exposed pad under the body).
- **Routed by a script.** The pcb skill says route by hand; with 120 nets over 112 x 236 mm, `scripts/routes.py` plans
  the wiring as an octolinear path search on a 0.1 mm grid (B.Cu and In2.Cu, a via costing 2.5 mm of track, nets that
  find no way ripped up with their neighbours and tried again), with the hand-placed pieces above. Every track is at a
  multiple of 45 degrees (`check_board.py`). It is a script's routing, not a person's: say so to whoever reviews it.

## Files

| Path | What |
| --- | --- |
| `build.py` | the one command that makes the KiCad project: every script below, in order |
| `scripts/geometry.py` | every place, from the design model: holes, combs, LEDs, the art clipped for the fab, the GPIO map, part places |
| `scripts/build_libraries.py` | the libraries from KiCad's stock ones, the combs' footprints from `playfield.py` |
| `scripts/schlib.py`, `scripts/schematic.py` | the schematic, as text |
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
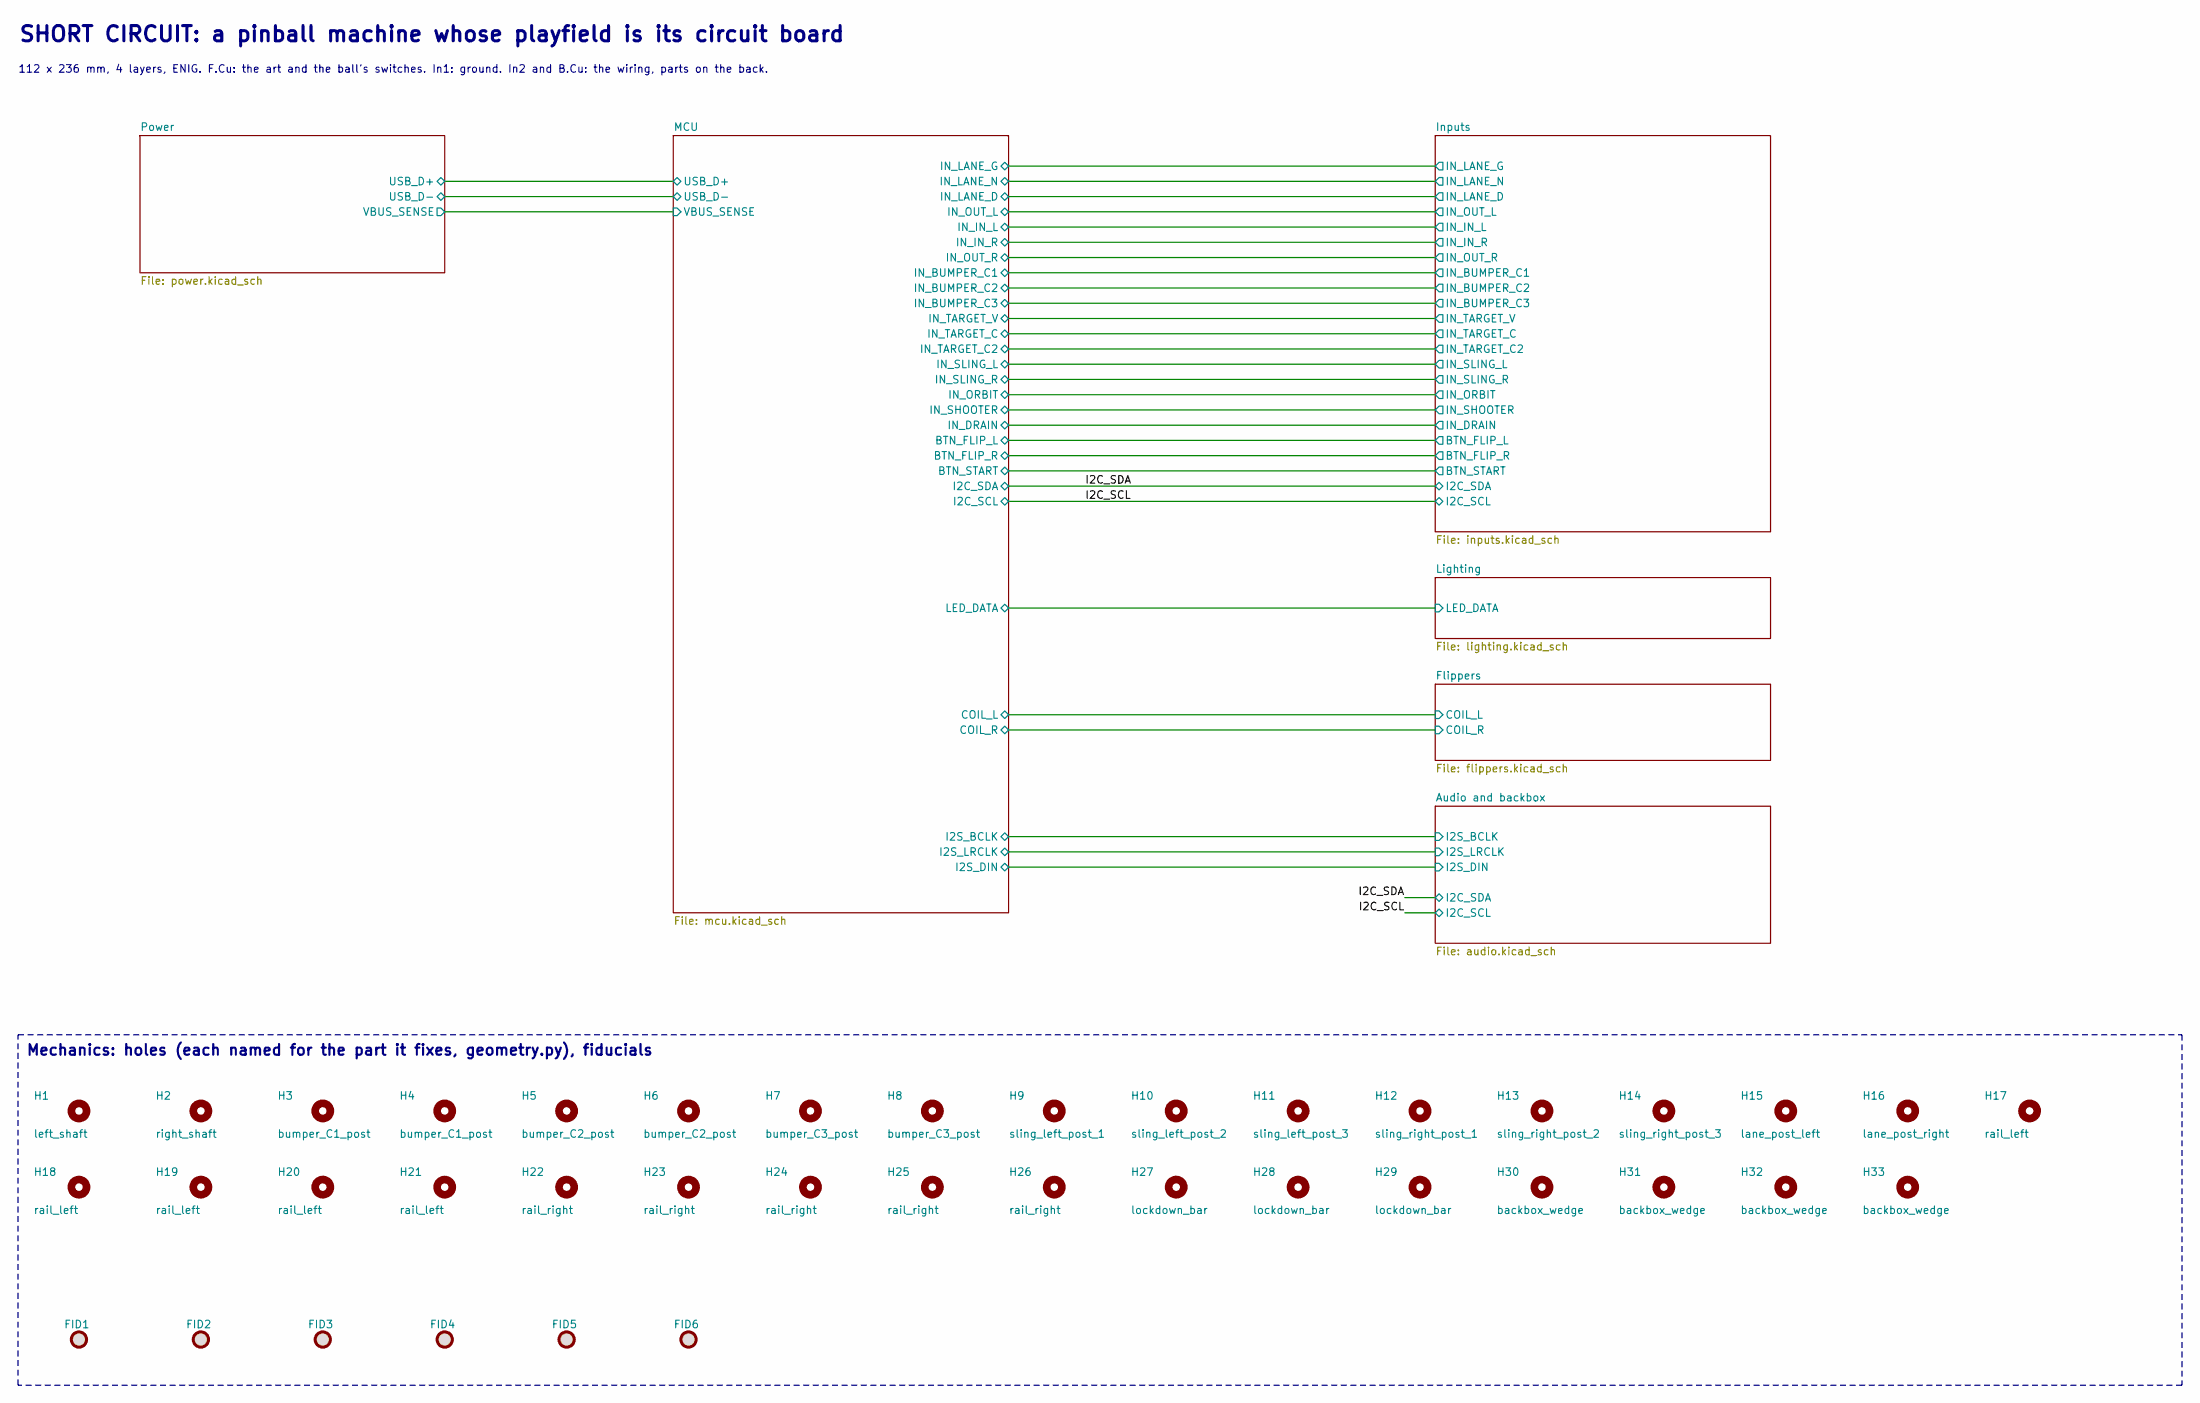
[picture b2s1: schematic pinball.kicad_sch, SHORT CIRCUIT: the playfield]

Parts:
FID1, FID2, FID3, FID4, FID5, FID6: Fiducial; Fiducial_1mm_Mask2mm
H1: left_shaft; NPTH_6.0mm
H2: right_shaft; NPTH_6.0mm
H3, H4: bumper_C1_post; NPTH_2.2mm
H5, H6: bumper_C2_post; NPTH_2.2mm
H7, H8: bumper_C3_post; NPTH_2.2mm
H9: sling_left_post_1; NPTH_2.2mm
H10: sling_left_post_2; NPTH_2.2mm
H11: sling_left_post_3; NPTH_2.2mm
H12: sling_right_post_1; NPTH_2.2mm
H13: sling_right_post_2; NPTH_2.2mm
H14: sling_right_post_3; NPTH_2.2mm
H15: lane_post_left; NPTH_2.2mm
H16: lane_post_right; NPTH_2.2mm
H17, H18, H19, H20, H21: rail_left; NPTH_2.2mm
H22, H23, H24, H25, H26: rail_right; NPTH_2.2mm
H27, H28, H29: lockdown_bar; NPTH_2.2mm
H30, H31, H32, H33: backbox_wedge; NPTH_2.2mm

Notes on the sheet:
SHORT CIRCUIT: a pinball machine whose playfield is its circuit board
112 x 236 mm, 4 layers, ENIG. F.Cu: the art and the ball's switches. In1: ground. In2 and B.Cu: the wiring, parts on the back.
Mechanics: holes (each named for the part it fixes, geometry.py), fiducials

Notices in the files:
README.md:
License: MIT
